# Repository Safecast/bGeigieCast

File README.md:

# bGeigieCast

An extension module to use your mobile bGeigieNano as a fixed sensor! 

User manual and other documentation on the Github Wiki:

* [User manual](https://github.com/Safecast/bGeigieCast/wiki/User-manual)
* [Quick start guide](https://github.com/Safecast/bGeigieCast/wiki/Quick-start-guide)
* [Set up your development environment](https://github.com/Safecast/bGeigieCast/wiki/Development-environment)

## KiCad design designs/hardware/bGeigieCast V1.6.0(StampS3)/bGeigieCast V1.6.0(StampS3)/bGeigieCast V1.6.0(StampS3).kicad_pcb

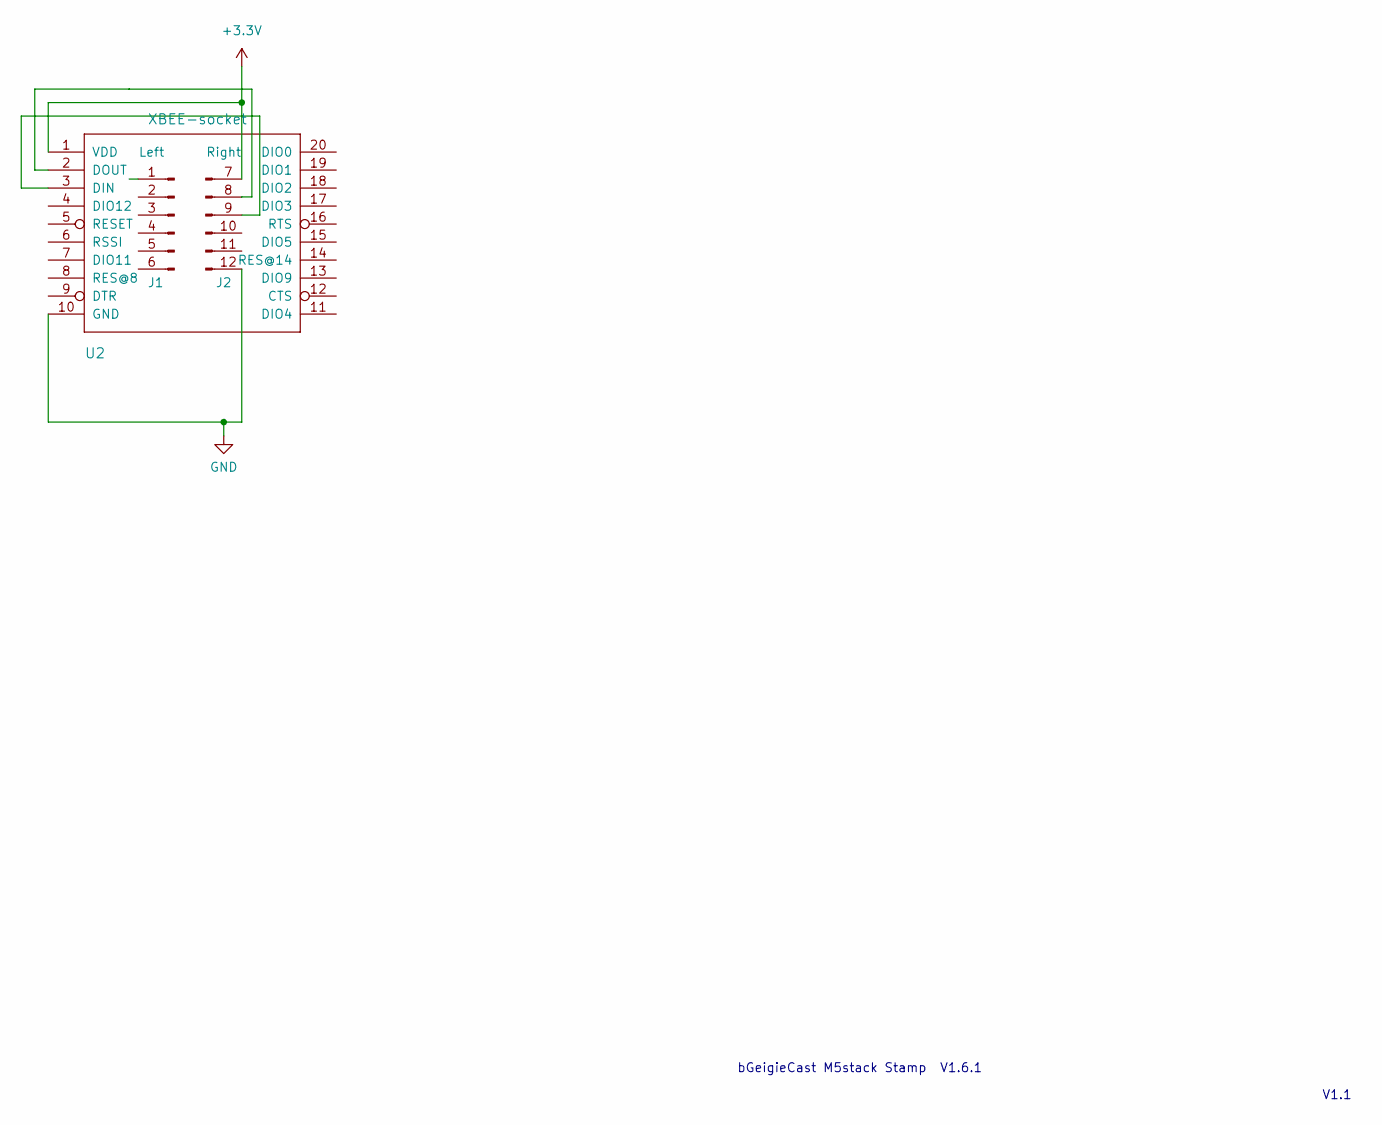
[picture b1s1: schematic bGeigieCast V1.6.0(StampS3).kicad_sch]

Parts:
J1: Left; PinHeader_1x09_P2.54mm_Vertical
J2: Right; PinHeader_1x06_P2.54mm_Vertical
U2: XBEE-socket; XBEE-20_THT

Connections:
+3.3V: J2.7, U2.1 (VDD)
GND: J2.12, U2.10 (GND)
unnamed: J2.8, U2.2 (DOUT)
unnamed: J2.9, U2.3 (DIN)

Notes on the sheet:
V1.1
bGeigieCast M5stack Stamp V1.6.1

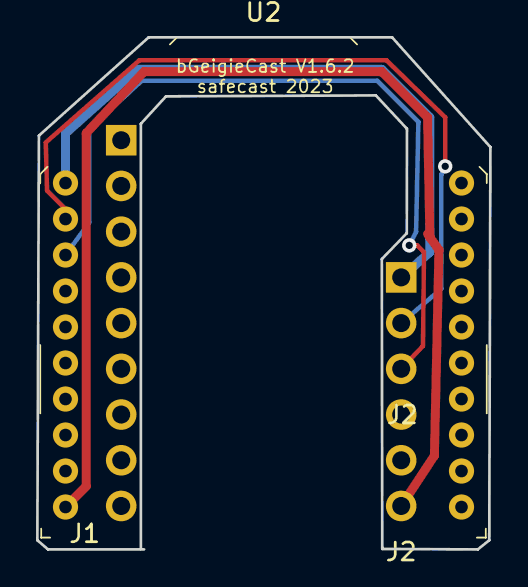
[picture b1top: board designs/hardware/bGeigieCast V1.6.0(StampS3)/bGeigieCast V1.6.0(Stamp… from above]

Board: 2 copper layers, 25.2 x 28.4 mm, 3 parts (0 on the bottom side), 4 nets.

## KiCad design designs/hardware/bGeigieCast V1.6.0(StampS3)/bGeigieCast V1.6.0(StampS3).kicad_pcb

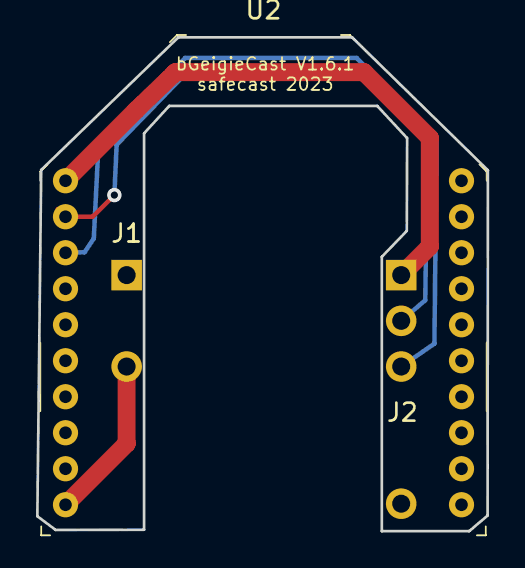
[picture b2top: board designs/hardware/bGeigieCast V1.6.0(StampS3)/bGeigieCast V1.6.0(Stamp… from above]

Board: 2 copper layers, 25.0 x 27.4 mm, 3 parts (0 on the bottom side), 4 nets.

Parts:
J1: Left; PinHeader_1x06_P2.54mm_Vertical
J2: Right; PinHeader_1x06_P2.54mm_Vertical
U2: XBEE-socket; XBEE-20_THT

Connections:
GND: J1.3, U2.10 (GND)
unnamed: J2.1, U2.1 (VDD)
unnamed: J2.2, U2.2 (DOUT)
unnamed: J2.3, U2.3 (DIN)

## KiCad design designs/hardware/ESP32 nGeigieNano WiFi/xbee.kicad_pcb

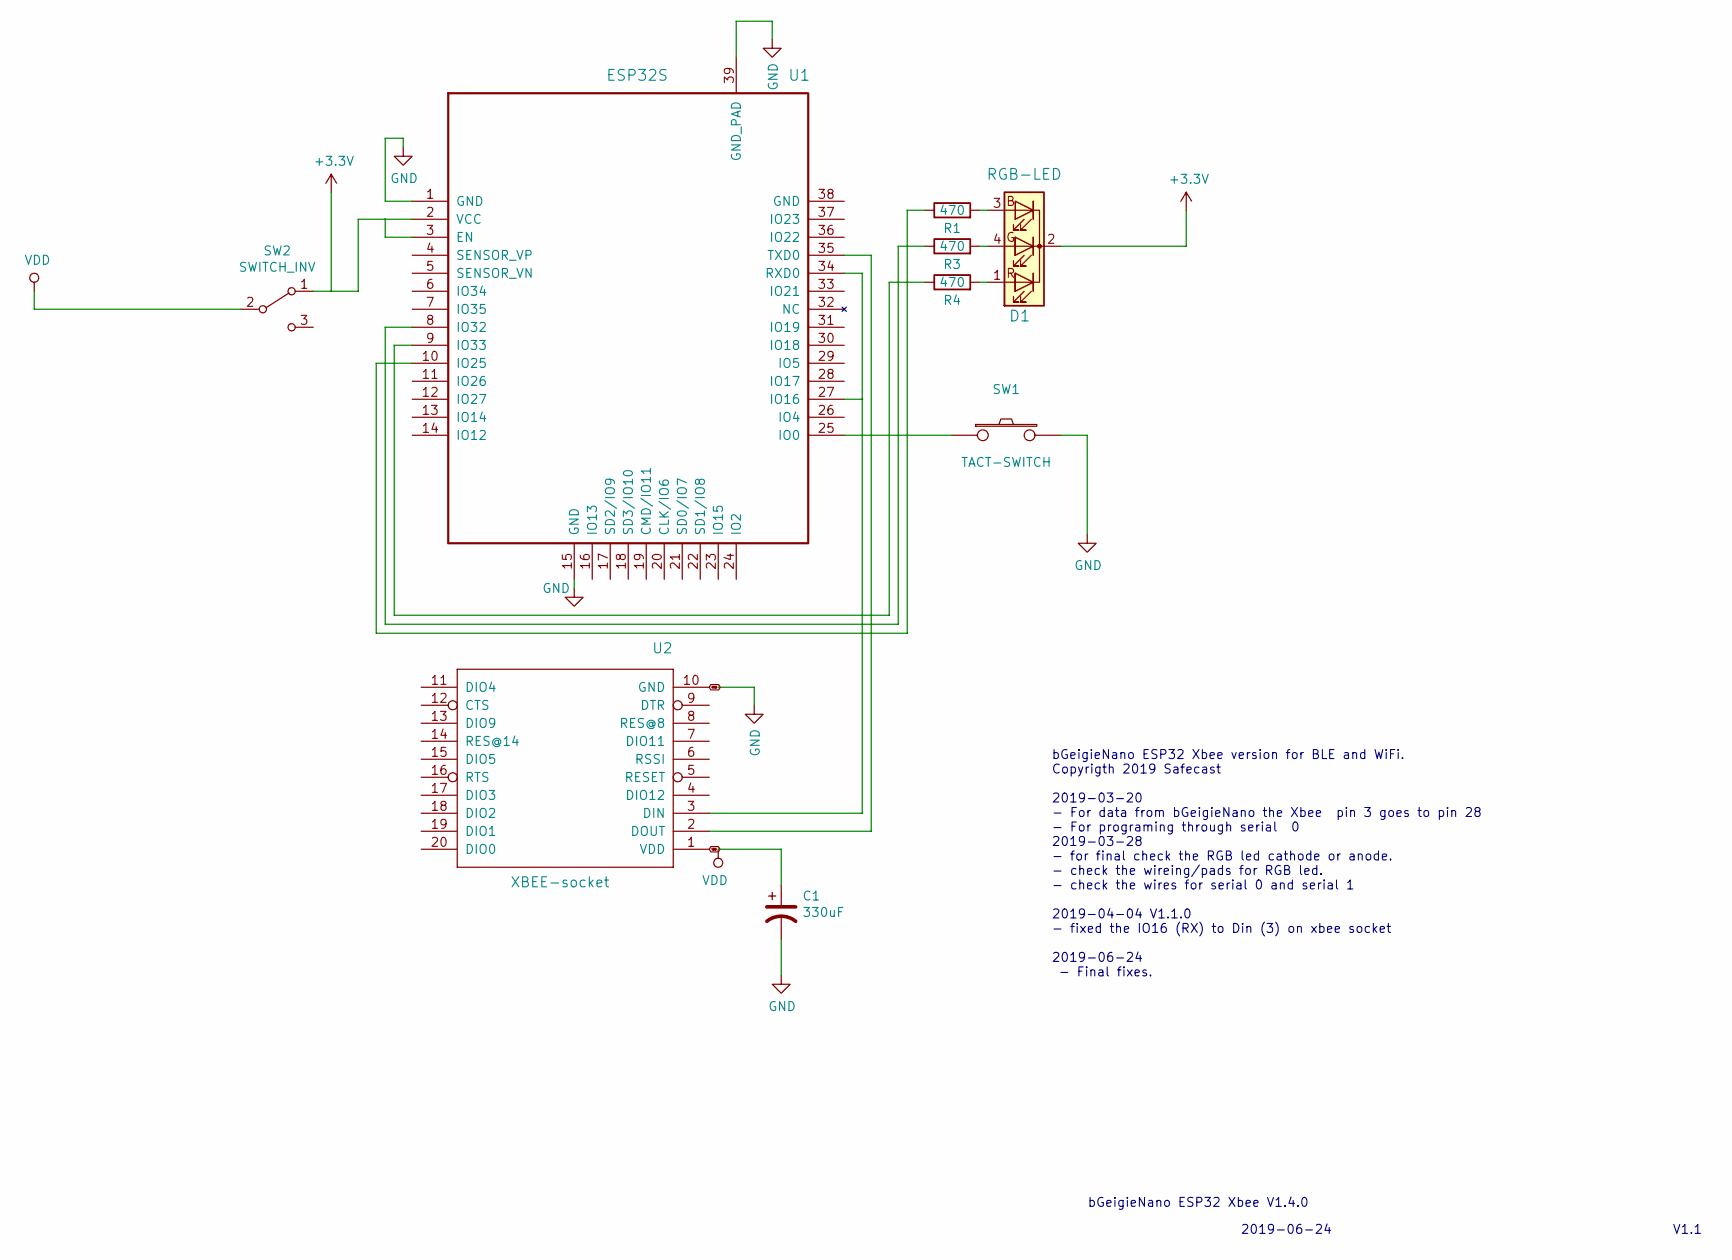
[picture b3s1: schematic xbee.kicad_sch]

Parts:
C1: 330uF; CP_EIA-6032-15_Kemet-U_Pad2.25x2.35mm_HandSolder
D1: RGB-LED; DJS-BRGBC-TR8
R1, R3, R4: 470; R_0805_HandSoldering
SW1: TACT-SWITCH; SW_SPST_TL3342
SW2: SWITCH_INV; SW_SPDT_PCM12
U1: ESP32S; ESP-32S
U2: XBEE-socket; XBEE-20_THT

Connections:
+3V3: D1.2 (K), SW2.1 (A), U1.2 (VCC), U1.3 (EN)
GND: C1.2, SW1.2, U1.1 (GND), U1.15 (GND), U1.39 (GND_PAD), U2.10 (GND)
unnamed: D1.1 (RA), R4.2
unnamed: D1.3 (BA), R1.2
unnamed: D1.4 (GA), R3.2
unnamed: R1.1, U1.10 (IO25)
unnamed: R3.1, U1.8 (IO32)
unnamed: R4.1, U1.9 (IO33)
unnamed: SW1.1, U1.25 (IO0)
unnamed: U1.27 (IO16), U1.34 (RXD0), U2.3 (DIN)
unnamed: U1.35 (TXD0), U2.2 (DOUT)
VDD: C1.1, SW2.2 (B), U2.1 (VDD)

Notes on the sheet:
bGeigieNano ESP32 Xbee version for BLE and WiFi. Copyrigth 2019 Safecast 2019-03-20 - For data from bGeigieNano the Xbee pin 3 goes to pin 28 - For programing through serial 0 2019-03-28 - for final check the RGB led cathode or anode. - check the wireing/pads for RGB led. - check the wires for seri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
bGeigieNano ESP32 Xbee V1.4.0
2019-06-24
V1.1

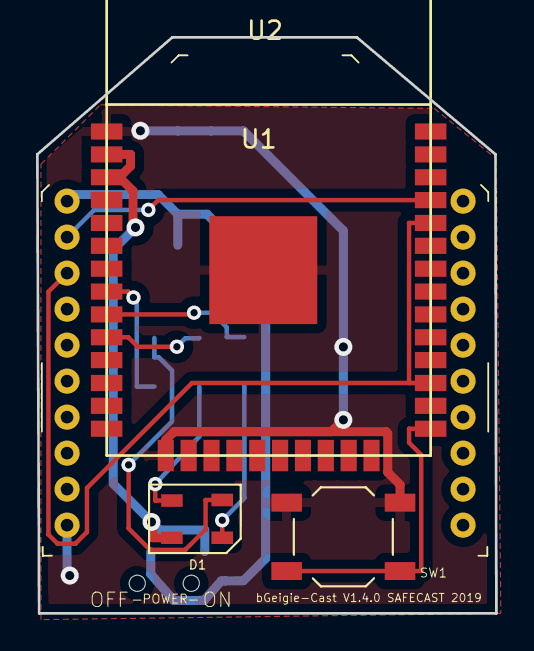
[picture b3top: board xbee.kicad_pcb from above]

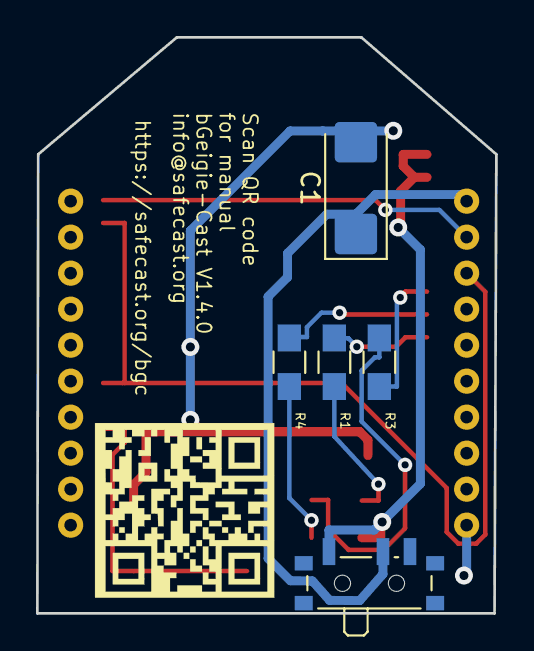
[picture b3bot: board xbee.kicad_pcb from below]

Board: 2 copper layers, 25.5 x 32.0 mm, 9 parts (5 on the bottom side), 12 nets.

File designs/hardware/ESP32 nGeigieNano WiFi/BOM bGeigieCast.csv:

Id,Designator,Package,Quantity,Designation,Supplier and ref,URL
6,C1,CP_EIA-6032-15_Kemet-U_Pad2.25x2.35mm_HandSolder,1,CP1,,
2,D1,DJS-BRGBC-TR8,1,RGB-LED,,
8,G***,QR_code_safecast_bgc,1,LOGO,,
7,"R1,R3,R4",R_0805_HandSoldering,3,470,,
1,SW1,SW_SPST_TL3342,1,TACT-SWITCH,,
5,SW2,SW_SPDT_PCM12,1,SWITCH_INV,,
4,U1,ESP-32S,1,ESP32S,,
3,U2,XBEE-20_THT,1,XBEE-socket,,https://www.sparkfun.com/products/10112

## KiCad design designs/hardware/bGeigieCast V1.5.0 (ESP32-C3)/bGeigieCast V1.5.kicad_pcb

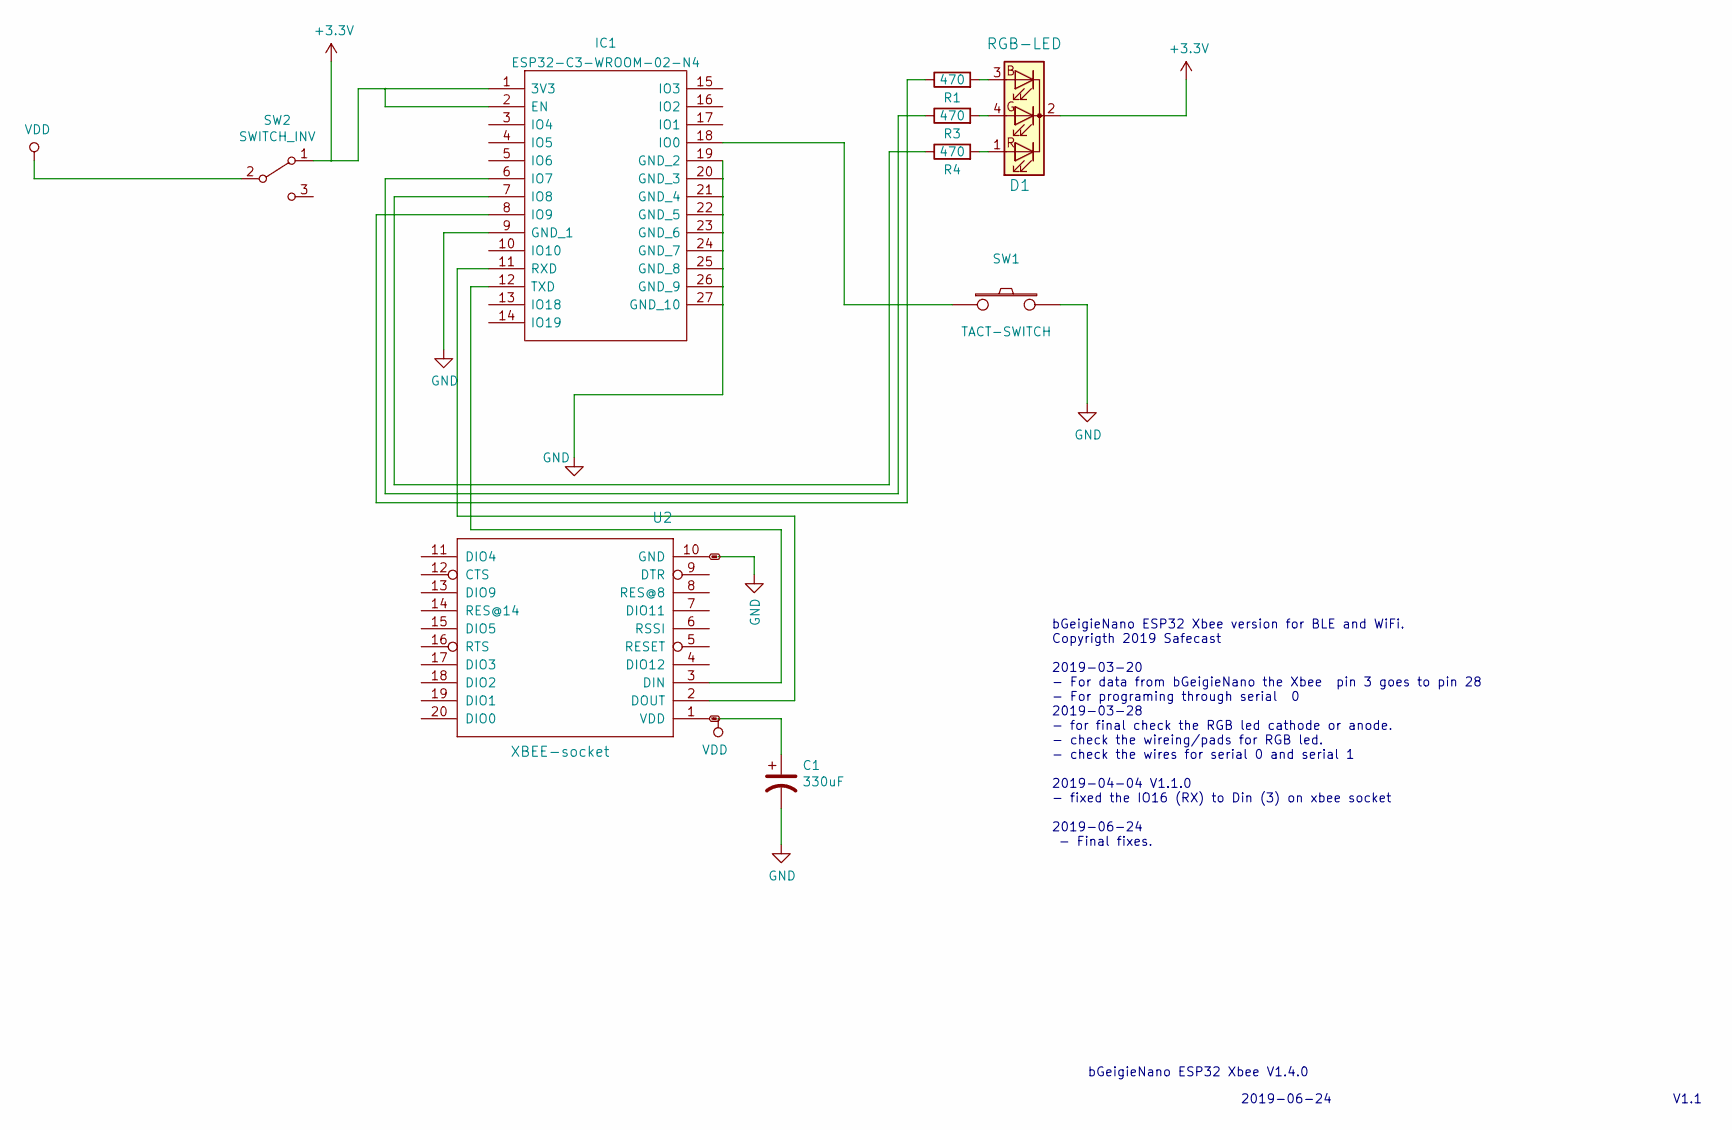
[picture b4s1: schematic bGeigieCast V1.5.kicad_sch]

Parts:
C1: 330uF; CP_EIA-6032-15_Kemet-U_Pad2.25x2.35mm_HandSolder
D1: RGB-LED; DJS-BRGBC-TR8
IC1: ESP32-C3-WROOM-02-N4; ESP32C3WROOM02N4; Manufacturer_Part_Number ESP32-C3-WROOM-02-N4; Mouser Part Number 356-ESP32C3WROOM02N4
R1, R3, R4: 470; R_0805_HandSoldering
SW1: TACT-SWITCH; SW_SPST_TL3342
SW2: SWITCH_INV; SW_SPDT_PCM12
U2: XBEE-socket; XBEE-20_THT

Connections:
+3V3: D1.2 (K), IC1.1 (3V3), IC1.2 (EN), SW2.1 (A)
GND: C1.2, IC1.9 (GND_1), IC1.19 (GND_2), IC1.20 (GND_3), IC1.21 (GND_4), IC1.22 (GND_5), IC1.23 (GND_6), IC1.24 (GND_7), IC1.25 (GND_8), IC1.26 (GND_9), IC1.27 (GND_10), SW1.2, U2.10 (GND)
unnamed: D1.1 (RA), R4.2
unnamed: D1.3 (BA), R1.2
unnamed: D1.4 (GA), R3.2
unnamed: IC1.8 (IO9), R1.1
unnamed: IC1.6 (IO7), R3.1
unnamed: IC1.7 (IO8), R4.1
unnamed: IC1.18 (IO0), SW1.1
unnamed: IC1.11 (RXD), U2.2 (DOUT)
unnamed: IC1.12 (TXD), U2.3 (DIN)
VDD: C1.1, SW2.2 (B), U2.1 (VDD)

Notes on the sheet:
bGeigieNano ESP32 Xbee version for BLE and WiFi. Copyrigth 2019 Safecast 2019-03-20 - For data from bGeigieNano the Xbee pin 3 goes to pin 28 - For programing through serial 0 2019-03-28 - for final check the RGB led cathode or anode. - check the wireing/pads for RGB led. - check the wires for seri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
bGeigieNano ESP32 Xbee V1.4.0
2019-06-24
V1.1

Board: 2 copper layers, 9 parts (5 on the bottom side), 12 nets, no tracks yet.

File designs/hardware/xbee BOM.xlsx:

bGeigieCast V1.4.0 BOM
Id | Designator | Package | Quantity | Designation | Supplier and ref | Price Japan | Subtotal | URL
1 | G*** | QR_code_safecast_bgc | 1 | LOGO |  |  | 0
2 | C1 | CP_Tantalum_Case-D_EIA-7343-31_Reflow | 1 | CP1 |  | 37 | 37 | https://www.ebay.com/itm/322335558548
3 | R4,R3,R1 | R_0805_HandSoldering | 3 | 470 |  | 1 | 3 | https://amazon.co.jp/
4 | U2 | XBEE-20_THT | 2 | XBEE-pins | Mouser | 65 | 130 | https://www.mouser.com/ProductDetail/Harwin/M22-2511005?qs=s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
5 | D1 | DJS-BRGBC-TR8 | 1 | RGB-LED | Switch Science | 280 | 280 | https://www.switch-science.com/catalog/81/
6 | U1 | ESP-32S | 1 | ESP32S | Banggood | 510 | 510 | https://www.banggood.com/ESP32-S-WiFi-bluetooth-ESP32S-Seria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
7 | SW2 | SW_SPDT_PCM12 | 1 | SWITCH_INV | Digikey | 101 | 101 | https://www.digikey.com/product-detail/en/c-k/PCM12SMTR/401-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
8 | SW1 | SW_SPST_TL3342 | 1 | TACT-SWITCH |  | 70 | 70 | https://www.mouser.com/ProductDetail/E-Switch/TL3342F160QG?q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
9 | Board | Dirty PCB 5x5 prototype gold | 1 |  |  | 540 | 540 | https://dirtypcbs.com/store/order/2055375/
 |  |  |  |  |  |  | 1671

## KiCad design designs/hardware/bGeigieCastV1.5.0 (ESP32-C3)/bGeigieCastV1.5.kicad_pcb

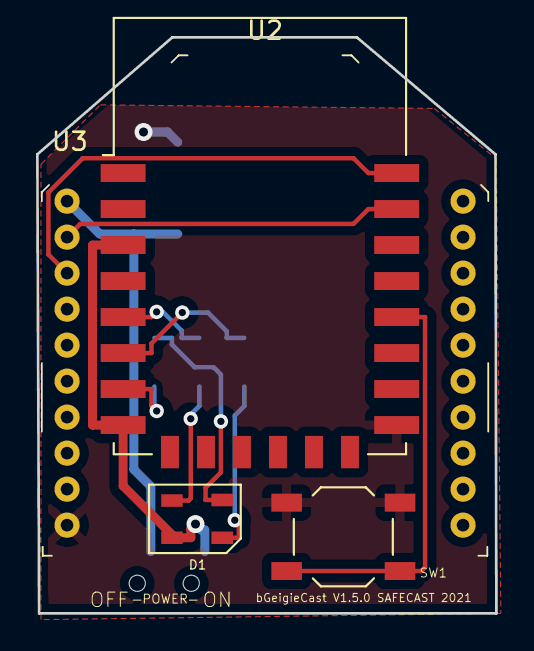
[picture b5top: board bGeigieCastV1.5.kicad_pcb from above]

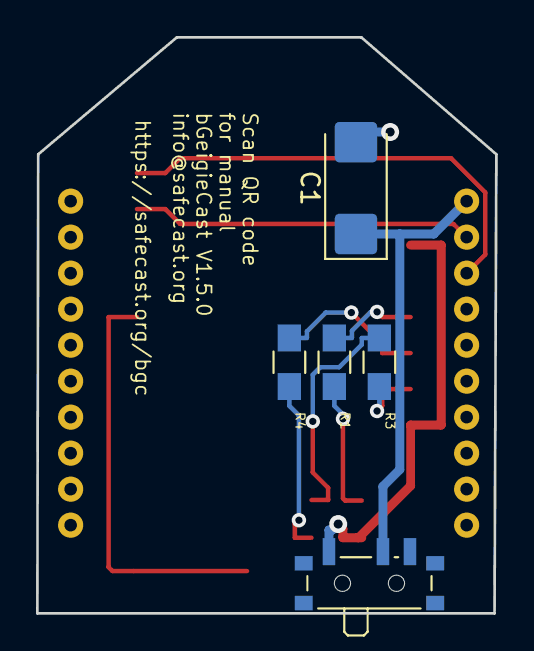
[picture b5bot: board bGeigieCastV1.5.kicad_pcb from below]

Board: 2 copper layers, 25.5 x 32.0 mm, 9 parts (5 on the bottom side), 12 nets.

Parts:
C1: 330uF; CP_EIA-6032-15_Kemet-U_Pad2.25x2.35mm_HandSolder
D1: RGB-LED; DJS-BRGBC-TR8
R1, R3, R4: 470; R_0805_HandSoldering
SW1: TACT-SWITCH; SW_SPST_TL3342
SW2: SWITCH_INV; SW_SPDT_PCM12
U2: XBEE-socket; XBEE-20_THT
U3: ESP-12E

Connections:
+3V3: D1.2 (K), SW2.1 (A), U3.3 (EN), U3.8 (VCC)
GND: C1.2, SW1.2, U2.10 (GND), U3.15 (GND)
unnamed: D1.1 (RA), R4.2
unnamed: D1.3 (BA), R1.2
unnamed: D1.4 (GA), R3.2
unnamed: R1.1, U3.5 (GPIO14)
unnamed: R3.1, U3.7 (GPIO13)
unnamed: R4.1, U3.6 (GPIO12)
unnamed: SW1.1, U3.18 (GPIO0)
unnamed: U2.2 (DOUT), U3.21 (GPIO3/RXD)
unnamed: U2.3 (DIN), U3.22 (GPIO1/TXD)
VDD: C1.1, SW2.2 (B), U2.1 (VDD)

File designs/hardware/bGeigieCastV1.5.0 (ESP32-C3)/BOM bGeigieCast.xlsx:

Id | Designator | Package | Quantity | Designation |  | Supplier and ref | URL | alt URL
6 | C1 | CP_EIA-6032-15_Kemet-U_Pad2.25x2.35mm_HandSolder | 1 | CP1 | 330uF 15V |  | https://www.ebay.com/itm/322335558548
2 | D1 | DJS-BRGBC-TR8 | 1 | RGB-LED | Common cathode |  | https://www.sparkfun.com/products/7844
8 | G*** | QR_code_safecast_bgc | 1 | LOGO
7 | R1,R3,R4 | R_0805_HandSoldering | 3 |  | 470 |  | https://www.amazon.com/470-ohm-Resistor-Resistors-Tolerance/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 | https://www.amazon.com/HiLetgo-Values-Resistors-Assortment-R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
1 | SW1 | SW_SPST_TL3342 | 1 | TACT-SWITCH |  |  | https://www.digikey.com/en/products/detail/e-switch/TL3342F1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
5 | SW2 | SW_SPDT_PCM12 | 1 | SWITCH_INV |  |  | https://www.digikey.com/en/products/detail/c-k/PCM12SMTR/164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
4 | U1 | ESP-32S | 1 | ESP32S |  |  | https://www.digikey.com/en/products/detail/espressif-systems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
3 | U2 | XBEE-20_THT | 1 | XBEE-socket | 2x10 2mm pitch |  | https://www.sparkfun.com/products/10112

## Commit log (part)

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2019-02-14 Added files
2019-02-14 add gitignore, add usecase diagram
2019-02-14 Added header with Copyrights
2019-02-14 webserver test branch
2019-02-14 Added Kicad files
2019-02-14 Update gitignore
2019-02-14 Added one more file to gitignore
2019-02-14 Added gitignore to master
2019-02-15 Added .vscode to gitignore (was every time coning back)
2019-02-15 Added .vscode to gitignore.
2019-02-15 One more cleanup
2019-02-15 cleanup
2019-02-15 added the files back to source
2019-02-15 Removed src files for master
2019-02-17 Added serial speed to platformIO inii
2019-02-18 update ucd
2019-02-18 update state diagram with transition and new idea for server
2019-02-21 update state machine
2019-02-22 add rest of the states; add button functionality
2019-02-24 fix bug in buffer
2019-02-24 move webserver to temp, fix compile warning in config
2019-02-25 Use api test address from settings
2019-02-25 move around source files to compile on arduino, (not compiling yet, but still works in PIO
2019-02-25 fix typo in schedule_event
2019-02-26 add unit tests for buffer, esp config class, some state transitions
2019-02-27 add clear events method
2019-02-27 update state transition unit tests
2019-02-27 remove autogenerated file...
2019-02-27 Added files for test in DEV-ROB
2019-02-27 updated ini.
2019-02-27 Added screenshot of board
2019-02-28 add readings class plus unit tests, tried to do some readings
2019-02-28 remove test output...
2019-03-01 fix float unit test in json
2019-03-01 clean up json method, update unit test for mobile mode
2019-03-03 update one json unittest to test negative lat long
2019-03-04 add reading merge, update implementation in controller for reading, add merge tests
2019-03-04 remove class diagram for now, still work in progress
2019-03-04 add bluetooth connector class, initial settings etc
2019-03-05 quick fix button unit tests
2019-03-05 Work in progress, pass reading to bluetooth
2019-03-05 work in progress
2019-03-05 cleanup code
2019-03-05 remove class diagram as its still work in progress
2019-03-06 remove temporary test code, cleanup member vars
2019-03-06 cleanup rest of the bluetooth temporary changes
2019-03-06 move delete reading from api only to always delete
2019-03-06 add some documentation to existing classes
2019-03-07 add api connector methods; change reading parameter from pointer to reference;
2019-03-07 initialize nullptr reading; update pio ini to set default baudrate
2019-03-07 call ttserve with reading; updated the lat/long parse, as well as the unit tests;
2019-03-08 add rgb led things for state changes
2019-03-08 add a test, rename esp led to rgb led
2019-03-08 quick bluetooth fixes
2019-03-09 working interrupt on mode button
2019-03-09 add post init state, start server now on button press after startup (in post init state), fix some button issues
2019-03-11 add defines for api values
2019-03-11 update controller state machine tests
2019-03-11 fix button unit test, fix initial state unit test
2019-03-11 cleanup bluetooth settings, using defines
2019-03-11 add http_request plus tests
2019-03-12 update config unit tests; save new configurations
2019-03-12 fix else statements in esp config; add ap configurations to config server; fix success message
2019-03-12 clean up config unit test..
2019-03-12 update one last unit test for parsing full request line
2019-03-12 Added new board Gerber files
2019-03-12 Added styling to the config page.( had to increase the transmtion lenght)
2019-03-12 LED common anode
2019-03-13 Setup for new hardware test
2019-03-13 tested the reconnect state with mobile network, add check for initial connect / else reconnect
2019-03-13 add check for correctly parsed reading before process
2019-03-13 Added set-up for esp32-wroom32
2019-03-13 update config defaults, add restart after reset
2019-03-13 update software design diagrams
2019-03-19 save state in config for restart; update state machine; state will now go to stationary by default after the config state (AP server)
2019-03-19 redo request query param getter; add variable for esp32 preference begin
2019-03-20 cleanup esp_config
2019-03-21 change the dataReport interface in the diagram, now provided by bGeigieController
2019-03-26 more injector patterns, cleanup code, change time checks to handle millis rollover, add stability check but needs final changes (used a custom time function before but didnt like it)
2019-03-26 fix lat / long conversion issue, add test for dms to dd conversion,
2019-03-26 update reading parse unit tests for new lat / long
2019-03-26 fix esp config test, which was still failing
2019-03-28 add LED config; update webserver to display led config and save on submit
2019-03-28 add color blind logic to the state led class
2019-03-28 add some random colors for color blind people
2019-03-28 shorten key name for intensity configuration
2019-03-28 update unit tests with new configurations
2019-03-28 update default LED intensity from 200 to 75
2019-04-06 added V1.1.0 of the boards.
2019-04-06 Updated user config info
2019-04-17 update designs
2019-04-17 move hardware to designs, rename diagrams to software, update software desgins
2019-04-17 move all to single directory
2019-04-18 Added V1.1.0 hardware changes
2019-04-19 add more states to the state machine, add all transitions
2019-04-19 Remove rob test credentials
2019-04-19 One more rob credentials removed
2019-04-22 working with new state implementations
2019-04-22 fix some transitions and add event schedules to the send reading to api
2019-04-30 Rob setup
2019-05-01 fix check from to ; save only reading that are 100% valid
2019-05-01 fix issue stuck in api failed state, update the sleep things
2019-05-02 remove access point ssid from config, add device id to config, add controller state init reading (between init and post init), add reporter init state to get the initial reading
2019-05-07 fix gps precision (bgeigie uses decimal minutes, not minutes seconds), update blink rate
2019-05-09 remove double check
2019-05-09 Added V1.2.0 gerbers
2019-05-13 change reading validity to status flags; merge logic updated, only merge gps/cpm if its available; updated checks before sending to api, reading needs to be valid ¨
2019-05-13 remove some code from another feature branch, remove old parser..
2019-05-13 change a word
2019-05-13 change word position to location
2019-05-13 save last location in memory instead of resetting it on startup...
2019-05-13 move conf page data to own file; fix gps precision issue; add method to apply home location to reading, revalidating it;
2019-05-14 add development api send frequency to the configurations, tested home location
2019-05-14 fix client stuck for real this time
2019-05-14 set alert flag on api initiate send #37
2019-05-15 move state implementation files to single concrete state file
2019-05-15 rename state led to mode led, so it doesnt confuse with the state machine files
2019-05-15 remove unused methods, remove old debug lines, fix LED turn off
2019-05-15 Added V1.2.0 gerber files
2019-05-15 Added BOM
2019-05-17 add some bgeigiecast images and photos
2019-05-17 rename file
2019-05-17 update led intensity
2019-05-17 fix intensity > 100 in rgb led
2019-05-20 more stable wifi connector
2019-05-21 work in progress, query params are available as arg
2019-05-21 working new config server
2019-05-22 connect to wifi for config, ota working
2019-05-23 cleanup changes
2019-05-27 fix saving config, cleaned up http pages
2019-05-28 V1.3.0 hardare board
2019-05-28 more work in progress
2019-05-29 remove test pages, add purecss styling to the config pages
2019-05-29 refacter contentbuffer, now pages only use a single buffer which saves 2kb mem
2019-06-06 add images for quick start guide
2019-06-07 fix segfault in rendering full config page, update update and other scripts (no longer requires jquery)
2019-06-07 small change to update page
2019-06-07 remove purecss file
2019-06-07 remove pre-compile platformio ino.cpp
2019-06-07 add quick start guide image: connection settings
2019-06-12 small quality changes
2019-06-14 add grafana quick start guide image
2019-06-17 fix critical error in the page rendering
2019-06-17 add dm_to_dd to lib tests, fix 2 mistakes in the reading tests
2019-06-17 update config tests
2019-06-17 update post init time to 4 seconds, add bGeigieCast version to landing page of conf server
2019-06-17 add some information on the landing page
2019-06-19 working http unit tests
2019-06-19 cleanup request tests
2019-06-19 cleanup request test
2019-06-27 Added latest Kicad files and Gerber files
2019-07-29 Add image for wiki, update firmware.bin (was not up to date with latest)
2019-08-18 update README with links to wiki
2019-12-07 refactored api connection (reading handling through references), remove send frequency setting
2019-12-07 re-add the api key to the post
2019-12-08 Measurement post working again, still bright flash on startup
2019-12-24 work in progress for separate api callback and multiple bluetooth states
2019-12-29 work in progress, restructured everything, missing led output and correct state transitions for controller
2019-12-29 add led defines
2019-12-30 config mode will now always use the access point, make config server available in fixed mode through wifi (if connected).
2019-12-30 cleanup, add transition from init directly to config mode (transition will happen after first reading has been read
2019-12-30 minor changes in html pages (breadcrubs to home, fix small inconvinience in the update script)
2019-12-30 add status page (not visible in menu yet, just dummy data)
2019-12-31 small changes to bluetooth activation / deactivation, better wifi reconnect
2020-01-03 add descriptions to configuration pages
2020-01-04 implementing the state transition to reset on long button press
2020-01-04 add grafana hyper link to homepage
2020-05-23 Added screenshots
2020-07-26 Wireless charger dock for QI
2020-10-03 updated files
2020-10-07 cleaned up Mac dot files
2021-04-10 Added bGigeiCast files to be implemented
2021-04-29 Update to upload lower speed while progamming
2021-06-23 Update V1.5.0 board
2021-06-28 some updates
2021-06-28 fixed home location calculation and usage
2021-06-29 Updated Firmware version and bin file.
2022-01-26 New branch for M5stamp pico
2022-02-28 Added the missing files
2022-03-01 Updated 3d models for board
2022-11-23 M5stack stamp start
2022-11-23 Created M5Stack_ stamp setup
2022-11-23 Efford to intergrade FastLed for led control
2023-01-04 Setup upload ports
2023-01-05 update V1.4.0 boards
2023-01-08 added LB branch
2023-01-10 Firware 1.2 and 1.3 added
2023-01-10 removed bgeigiezen code
2023-01-10 updated command line programing to V1.3
2023-06-27 add additional gps checks for measurements, add config server option to disable in fixed mode, fix response handle code
2023-06-27 add new firmware.bin version
2023-06-28 add LED support for gps errors (blink red) / sensor errors (solid red); cleanup code;
2023-06-29 updated schematic
2023-07-16 addde workspace
2023-07-18 Test for M5stampS3
2023-07-23 Platfomio chnage to atoms3
2023-07-28 Added V1.6.0 board
2023-07-28 Cleaned up the old files
2023-08-01 Added notes for serial ports.
2023-08-01 add buildflags m5stamp rx/tx, set debugger serial to USBSerial
2023-08-04 Changed userconfig anf platformIO.ini
2023-08-04 tested for serial out of Pico
2023-08-05 change button pin, fix led
2023-08-05 Used ATOM board in platformio.ini
2023-08-05 Disabled the debugger..
2023-08-05 Cleaned out the serial test
2023-08-05 Cleaned up old code
2023-08-05 test 2
2023-08-06 Updated platformio.ini
2023-08-08 Updated board
2023-08-08 update board and serial options for pico
2023-08-09 Updated debug stuff
2023-08-16 Updated StampS3 setup
2023-08-16 Added V1.6.1 boards
2023-09-07 Added V1.6.2 Gerbers and many boards updates.
2025-07-25 update with M5StampS3a
